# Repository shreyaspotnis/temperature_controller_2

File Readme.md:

# Temperature Controller 2

Bipolar output stage temperature controller with an accurate temperature
sensor.

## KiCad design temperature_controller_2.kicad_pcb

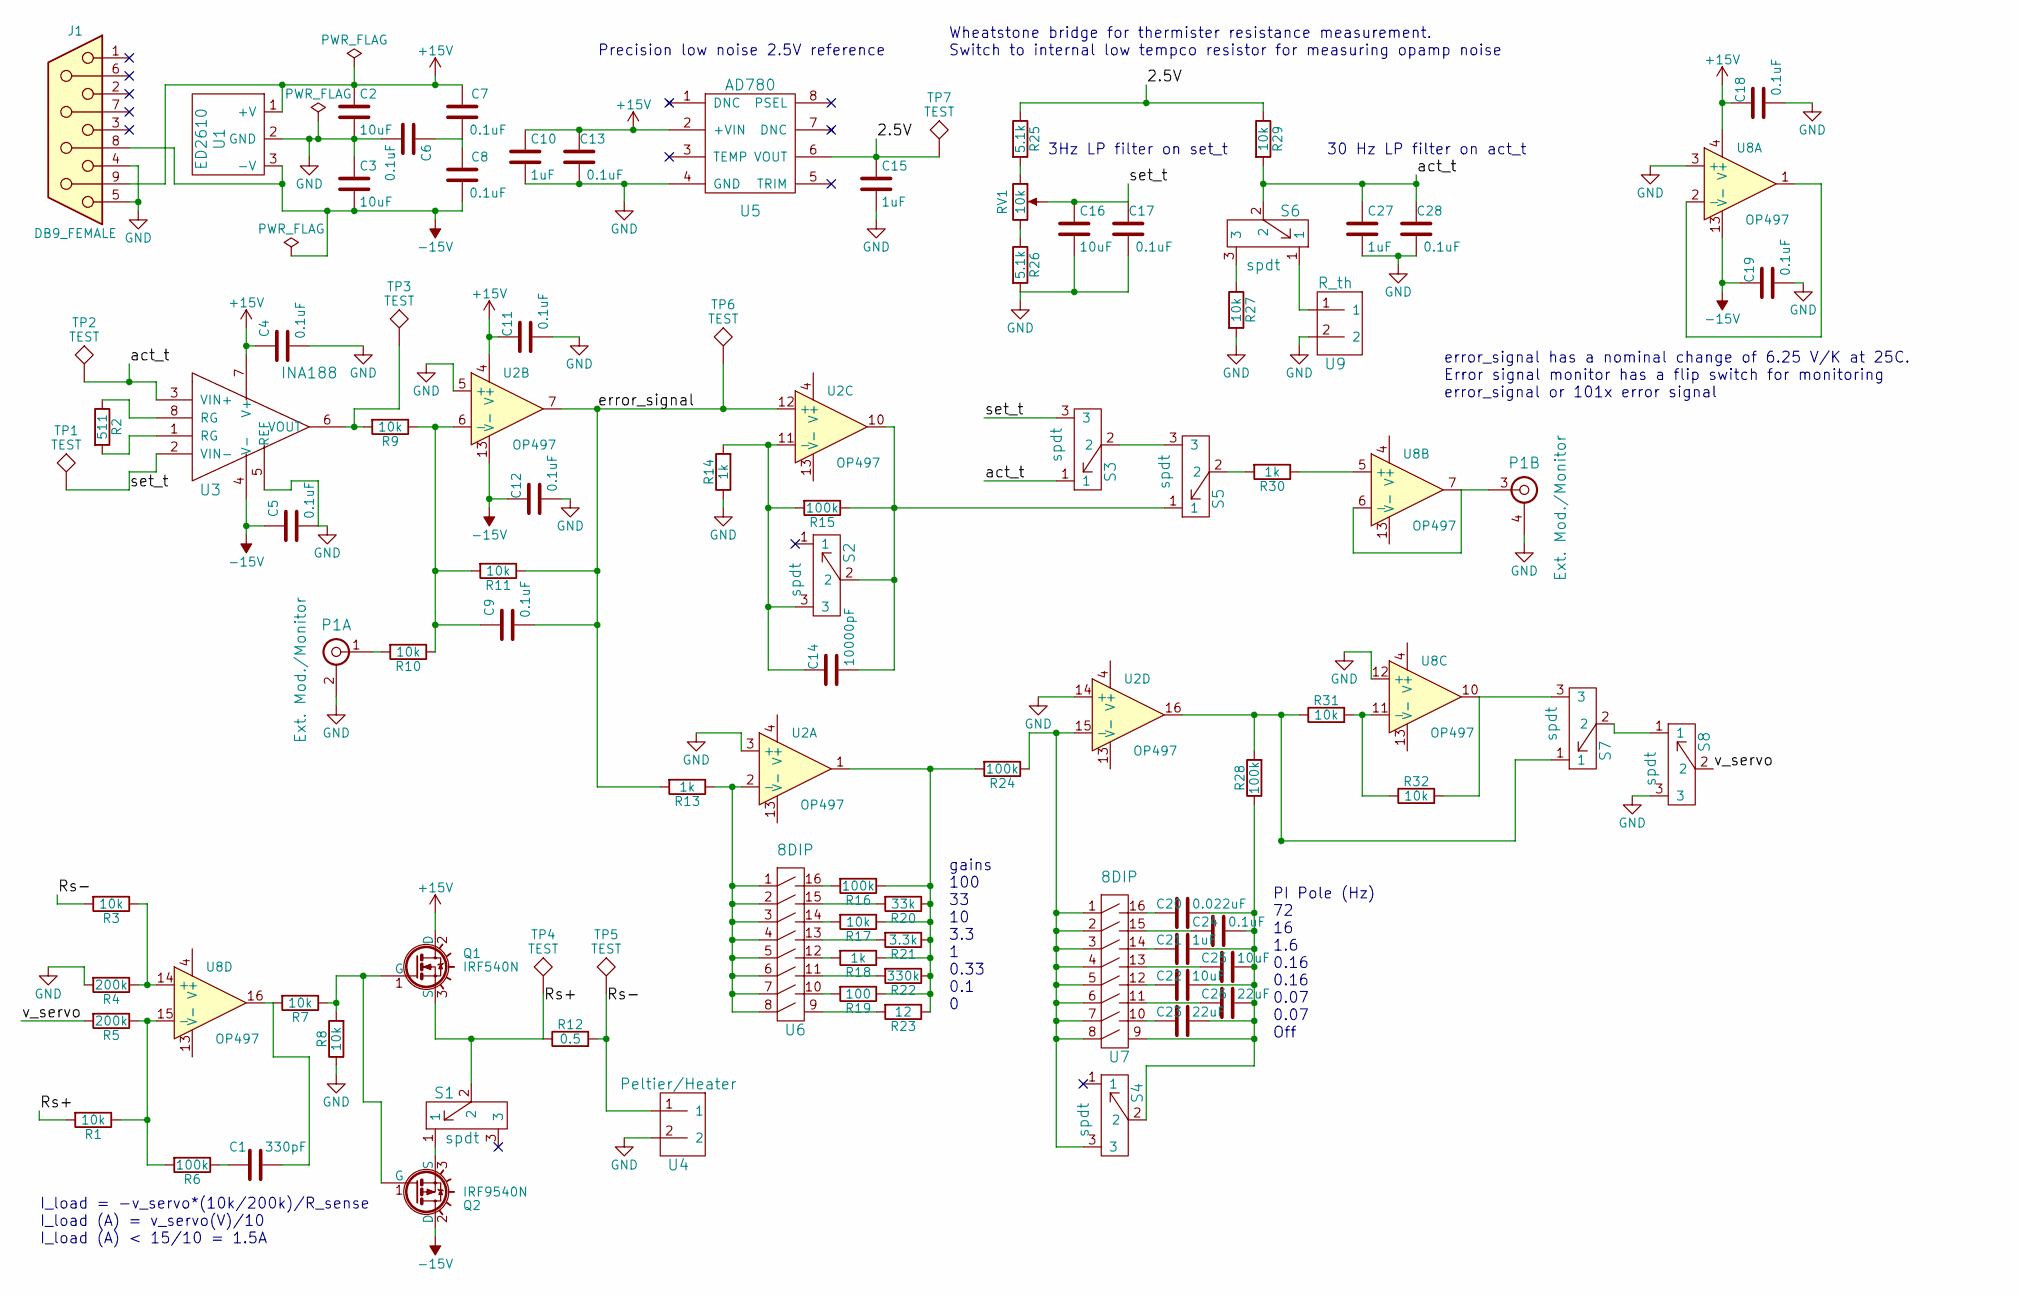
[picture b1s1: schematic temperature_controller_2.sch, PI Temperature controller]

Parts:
C1: 330pF; C_0603_HandSoldering
C2, C3, C16, C22, C25: 10uF; C_0603_HandSoldering
C4, C5, C6, C7, C8, C9, C11, C12, C13, C17, C18, C19, C24, C28: 0.1uF; C_0603_HandSoldering
C10, C15, C21, C27: 1uF; C_0603_HandSoldering
C14: 10000pF; C_0603_HandSoldering
C20: 0.022uF; C_0603_HandSoldering
C23, C26: 22uF; C_1206_HandSoldering
J1: DB9_FEMALE; DB9_Throughhole
P1: Ext. Mod./Monitor; Dual-BNC-ARF2136
Q1: IRF540N; TO-220_Vertical
Q2: IRF9540N; TO-220_Vertical
R1, R3, R7, R8, R9, R10, R11, R17, R27, R29, R31, R32: 10k; R_0603_HandSoldering
R2: 511; R_0603_HandSoldering
R4, R5: 200k; R_0603_HandSoldering
R6, R15, R16, R24, R28: 100k; R_0603_HandSoldering
R12: 0.5; R_2512_HandSoldering
R13, R14, R18, R30: 1k; R_0603_HandSoldering
R19: 100; R_0603_HandSoldering
R20: 33k; R_0603_HandSoldering
R21: 3.3k; R_0603_HandSoldering
R22: 330k; R_0603_HandSoldering
R23: 12; R_0603_HandSoldering
R25, R26: 5.1k; R_0603_HandSoldering
RV1: 10k; VishaySpectrol536
S1, S6, S7: spdt; CJS-1200TB-SPDT
S2, S3, S4, S5, S8: spdt; SPDT-Horizontal
TP1, TP2, TP3, TP4, TP5, TP6, TP7: TEST; Measurement_Point_Round-SMD-Pad_Small
U1: ED2610
U2, U8: OP497; SOIC-16W_7.5x10.3mm_Pitch1.27mm
U3: INA188; SOIC-8_3.9x4.9mm_Pitch1.27mm
U4: Peltier/Heater; ED2580
U5: AD780; SOIC-8_3.9x4.9mm_Pitch1.27mm
U6, U7: 8DIP; 8_POS_DIP_Switch
U9: R_th; ED2580

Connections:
+15V: C2.1, C4.2, C7.2, C10.1, C11.2, C13.2, C18.2, J1.9, Q1.2 (D), U1.1 (+V), U2.4 (V+), U3.7 (V+), U5.2 (+VIN), U8.4 (V+)
-15V: C3.2, C5.2, C8.1, C12.2, C19.2, J1.8, Q2.2 (D), U1.3 (-V), U2.13 (V-), U3.4 (V-), U8.13 (V-)
/2.5V: C15.1, R25.1, R29.1, TP7.1, U5.6 (VOUT)
/Rs+: Q1.3 (S), R1.2, R12.1, S1.2, TP4.1
/Rs-: R3.2, R12.2, TP5.1, U4.1
/act_t: C27.1, C28.2, R29.2, S3.1, S6.2, TP2.1, U3.3 (VIN+)
/error_signal: C9.1, R11.1, R13.2, TP6.1, U2.7, U2.12 (+)
/set_t: C16.1, C17.2, RV1.2, S3.3, TP1.1, U3.2 (VIN-)
/v_servo: R5.2, S8.2
GND: C2.2, C3.1, C4.1, C5.1, C6.2, C10.2, C11.1, C12.1, C13.1, C15.2, C16.2, C17.1, C18.1, C19.1, C27.2, C28.1, J1.4, J1.5, P1.2, P1.4, R4.2, R8.1, R14.1, R26.2, R27.2, S8.3, U1.2 (GND), U2.3 (+), U2.5 (+), U2.14 (+), U3.5 (REF), U4.2, U5.4 (GND), U8.3 (+), U8.12 (+), U9.2
unnamed: C1.1, R7.2, U8.16
unnamed: C1.2, R6.1
unnamed: C6.1, C7.1, C8.2
unnamed: C9.2, R9.1, R10.1, R11.2, U2.6 (-)
unnamed: C14.1, R15.1, S2.2, S5.1, U2.10
unnamed: C14.2, R14.2, R15.2, S2.3, U2.11 (-)
unnamed: C20.1, C21.1, C22.1, C23.1, C24.1, C25.1, C26.1, R28.1, S4.2, U7.9
unnamed: C20.2, U7.16
unnamed: C21.2, U7.14
unnamed: C22.2, U7.12
unnamed: C23.2, U7.10
unnamed: C24.2, U7.15
unnamed: C25.2, U7.13
unnamed: C26.2, U7.11
unnamed: P1.1, R10.2
unnamed: P1.3, U8.6 (-), U8.7
unnamed: Q1.1 (G), Q2.1 (G), R7.1, R8.2
unnamed: Q2.3 (S), S1.1
unnamed: R1.1, R5.1, R6.2, U8.15 (-)
unnamed: R2.1, U3.8 (RG)
unnamed: R2.2, U3.1 (RG)
unnamed: R3.1, R4.1, U8.14 (+)
unnamed: R9.2, TP3.1, U3.6 (VOUT)
unnamed: R13.1, U2.2 (-), U6.1, U6.2, U6.3, U6.4, U6.5, U6.6, U6.7, U6.8
unnamed: R16.1, R17.1, R18.1, R19.1, R20.1, R21.1, R22.1, R23.1, R24.2, U2.1
unnamed: R16.2, U6.16
unnamed: R17.2, U6.14
unnamed: R18.2, U6.12
unnamed: R19.2, U6.10
unnamed: R20.2, U6.15
unnamed: R21.2, U6.13
unnamed: R22.2, U6.11
unnamed: R23.2, U6.9
unnamed: R24.1, S4.3, U2.15 (-), U7.1, U7.2, U7.3, U7.4, U7.5, U7.6, U7.7, U7.8
unnamed: R25.2, RV1.1
unnamed: R26.1, RV1.3
unnamed: R27.1, S6.3
unnamed: R28.2, R31.1, S7.1, U2.16
unnamed: R30.1, U8.5 (+)
unnamed: R30.2, S5.2
unnamed: R31.2, R32.1, U8.11 (-)
unnamed: R32.2, S7.3, U8.10
unnamed: S3.2, S5.3
unnamed: S6.1, U9.1
unnamed: S7.2, S8.1
unnamed: U8.1, U8.2 (-)

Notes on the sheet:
Precision low noise 2.5V reference
Wheatstone bridge for thermister resistance measurement. Switch to internal low tempco resistor for measuring opamp noise
gains 100 33 10 3.3 1 0.33 0.1 0
PI Pole (Hz) 72 16 1.6 0.16 0.16 0.07 0.07 Off
error_signal has a nominal change of 6.25 V/K at 25C. Error signal monitor has a flip switch for monitoring error_signal or 101x error signal
30 Hz LP filter on act_t
3Hz LP filter on set_t
I_load = -v_servo*(10k/200k)/R_sense I_load (A) = v_servo(V)/10 I_load (A) < 15/10 = 1.5A

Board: 2 copper layers, 89 parts (5 on the bottom side), 56 nets, no tracks yet.

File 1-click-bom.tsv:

References	Qty	Description  Digikey
C1	1	C 330pF Unpolarized capacitor 0603 X7R  1276-6658-1-ND
C2, C3, C16, C25, C22	5	C 10uF Unpolarized capacitor 0603 X5R 490-7202-1-ND
C6, C7, C8, C13, C17, C28, C4, C5, C11, C12, C18, C19, C24, C9	14	C 0.1uF Unpolarized capacitor 0603 X7R 311-1088-1-ND
C10, C15, C27, C21	4	C 1uF Unpolarized capacitor 0603 X5R   587-1248-6-ND
C14	1	C 10000pF Unpolarized capacitor 0603 X7R  311-1085-1-ND
C20	1	C 0.022uF Unpolarized capacitor 0603 X7R  1276-1104-1-ND
C23, C26	2	C 22uF Unpolarized capacitor 1206 X5R 490-10755-1-ND
P1	1	Dual-BNC Ext. Mod./Monitor
Q1	1	IRF540N 100V Vds, 33A Id, HEXFET N-Channel MOSFET, TO-220 Vertical
Q2	1	IRF9540N -100V Vds, -23A Id, HEXFET P-Channel MOSFET, TO-220 Vertical
R2	1	R 511 Resistor
R4, R5	2	R 200k Resistor
R12	1	R 0.5 Resistor
R14, R13, R18, R30	4	R 1k Resistor
R15, R16, R24, R28, R6	5	R 100k Resistor
R19	1	R 100 Resistor
R20	1	R 33k Resistor
R21	1	R 3.3k Resistor
R22	1	R 330k Resistor
R23	1	R 12 Resistor
R25, R26	2	R 5.1k Resistor
R29, R27, R9, R11, R10, R17, R31, R32, R3, R7, R8, R1   12  10k resistor
RV1 1   POT 10k Potentionmeter
S1, S6, S7  3   spdt-onboard    563-1022-2-ND
S6, S3, S2, S5, S4, S7, S8, S1	8	spdt   switch  EG2362-ND
TP2, TP1, TP3, TP6, TP7, TP4, TP5	7	TEST Testpoint, connection for test equipment
U1	1	ED2610 3-pin wire to board ED2610-ND
U2, U8	2	OP497 Quad Op amp. OP497GSZ-ND
U3	1	INA188 Zero-drift in-amp   296-43151-1-ND
U5	1	AD780  2.5 V reference IC  AD780ARZ-ND
U6, U7	2	8DIP switch
U9, U4	2	ED2580 R th wire to board  ED2580-ND

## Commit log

2017-04-21 Init basic project structure.
2017-04-21 Power filtering added.
2017-04-21 Added 2.5V referece.
2017-04-23 Schematic completed.
2017-04-23 Footprints assigned.
2017-04-23 PCB component layout, first pass.
